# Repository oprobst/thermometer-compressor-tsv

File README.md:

# thermometer-compressor-tsv

Basicly this is a thermometer. It measures up to 3 values within a hirh range of (min. -50 to 350 degrees) using Thermoelement sensors. Additionally a port for DS18B20 is implemented (usually -55 to 125 degrees).
It is equiped with a display and a hard coded alarm limit.

Major requirement is to keep it simple (pure arduino code only) and modular (modules should be easy replaceable).

# Software

I kept the whole logic in this single script to make it easily adjustable for beginners. So there is just one arduino file.

## Arduino libraries in use
* U8g2 (version 2.28.10) Control LCD Display with ST7820 driver.
* OneWire (version 2.3.5) OneWire Bus protocol and driver.
* DallasTemperature (version 3.9.0) Helper library to maintain DS18S20 Temperature sensor.
* Adafruit MAX31855K (version 1.3.0) For reading the MAX 31855K Temperature sensors
* Adafruit BusIO (version 1.7.2) dependency of Adafruit MAX31855 library.

## Functionality

In general, this script consists of 3 major parts:

  1. Get temperature from a bunch of Dallas DS18B20 OneWires sensors. 
     These sensors usually range from -55 ... +85 °C, which is fine for room and outdoor temperature.
  2. Get up to 3 temperatures from K-Typ Thermoelements connected to the µController by a MAX31855 Chip . 
     The design focus on breakout modules easily be added to the ciruit and are replaceable in case of a defect.
     Range depends on type, up to > +1000 °C.
  3. A UI part for a display via the U8g2 lib.

## Components
Goal is to keep the amount of soldered component small and to use standardized plug-in modules. They can be replaced in case of a damage.

### Moduls
* [Arduino Nano (or clone)](https://www.reichelt.de/arduino-nano-v3-atmega-328-mini-usb-arduino-nano-p142943.html?PROVID=2788&gclid=Cj0KCQjw3duCBhCAARIsAJeFyPWbRqnDvxeFE9hGWIxeH9UpAeioCHqXIbZ7PTT7xyMbCtL9xDiokTYaAkQkEALw_wcB)
* [LCD Display 20x4 Character ](https://eckstein-shop.de/Graphic-128x64-LCD-Display-Module-12864-White-on-Blue-5V-Header-Strip?curr=EUR&gclid=Cj0KCQjw3duCBhCAARIsAJeFyPV9fqUd5TVanYePv4DA6xzIegzKWH7t7PSGK8yXDp_RgOqrNXzDfOYaAqsnEALw_wcB)
* 3x [Thermosensor MAX31855 Module](https://www.androegg.de/?product=max31855-k-type-temperatur-sensor-spi-konverter-modul)
* 3x [Rohranlegefühler Typ K (or similar)](https://www.sensorshop24.de/rohranlegefuehler-mit-alu-prisma-mit-nicr-ni-typ-k)
* [12V buzzer](https://www.conrad.de/de/p/tru-components-1567766-piezo-signalgeber-geraeusch-entwicklung-105-db-spannung-12-v-intervallton-1-st-1567766.html)

### On Board
|  ID  | Description |
| --- | -------- |
| R1 | 4,7 kOhm |
| R2 | 150 Ohm  |
| R3 | 10 kOhm  |
| R4 | 10 kOhm Potentiometer (optional) If display circuit has none included |
| U1 | [N-Channel Mosfet](https://www.conrad.de/de/p/infineon-technologies-irlz44npbf-mosfet-1-hexfet-110-w-to-220-162877.html) with 5V Logic-Level Gate |
| IC1 | 7805 Linear Regulator or 5V Output DC/DC Regulator |
| C1 | 330 nF Ceramic Condensator |
| C2 | 100 nF Ceramic Condensator |
| C4 | 220 µF Electrolyte Condensator |
| D1 | 1N4007 Diode |

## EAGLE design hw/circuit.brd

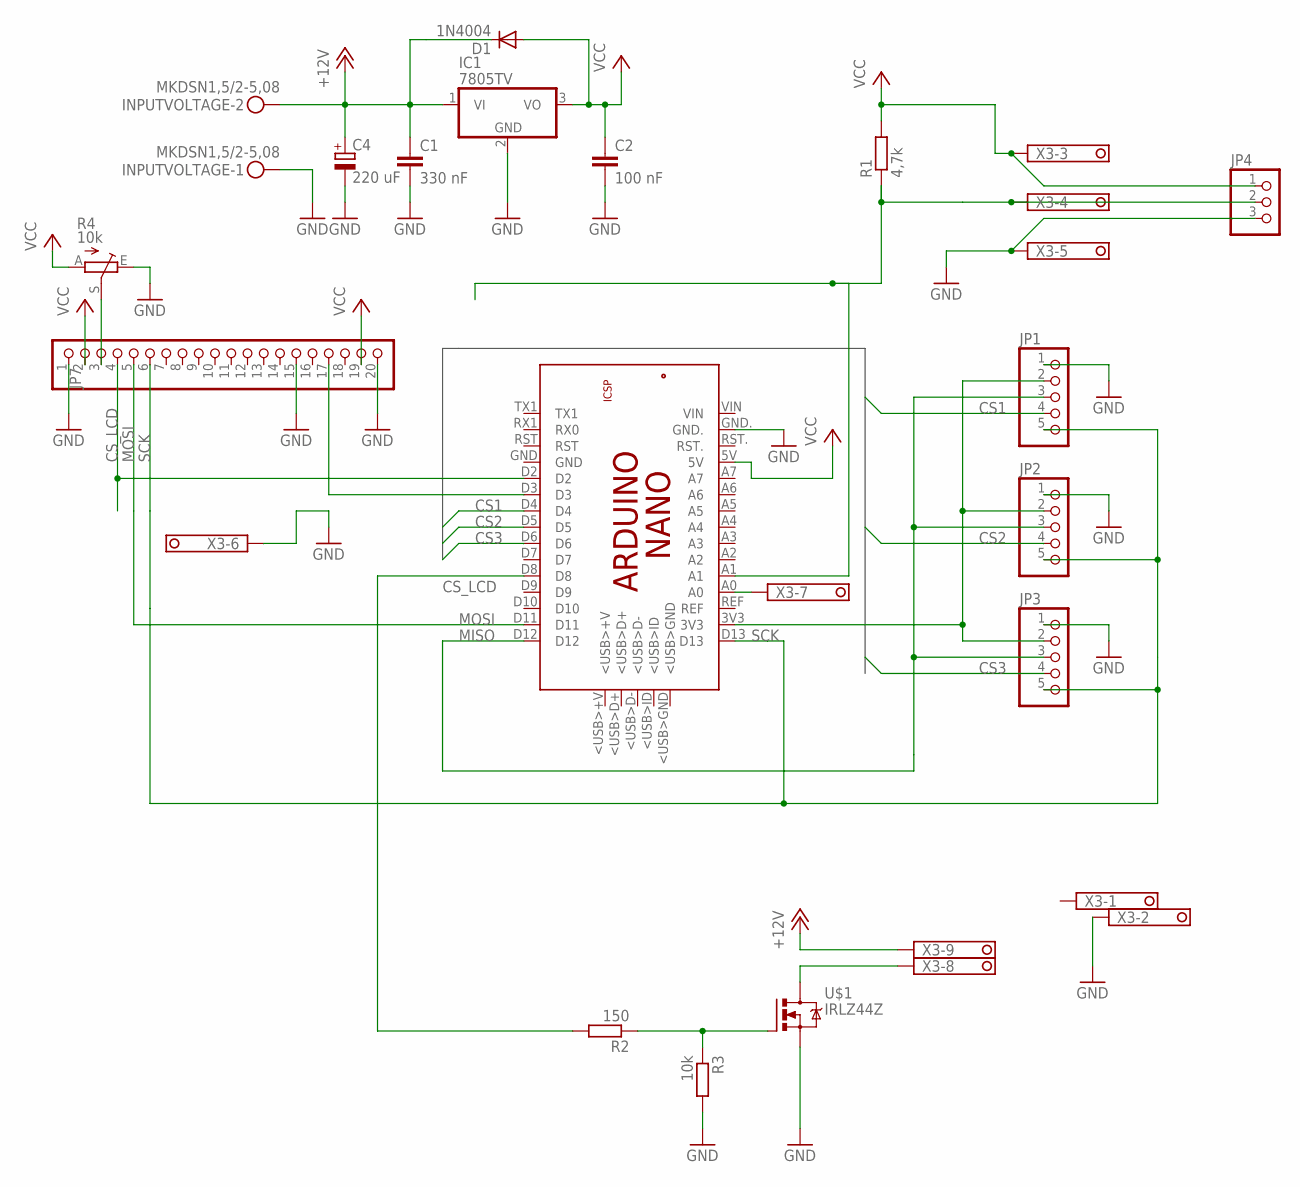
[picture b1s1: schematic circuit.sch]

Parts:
C1: 330 nF; C1206
C2: 100 nF; C0603
C4: 220 uF; E3,5-8
D1: 1N4004; DO41-10
IC1: 7805TV; TO220V
INPUTVOLTAGE: MKDSN1,5/2-5,08
JP1, JP2, JP3: PINHD-1X5; 1X05
JP4: PINHD-1X3; 1X03
JP7: PINHD-1X20; 1X20
PCB1: ARDUINO_NANO
R1: 4,7k; 0309/12
R2: 150; 0309/12
R3: 10k; 0309/12
R4: 10k; B64Y
U$1: IRLZ44Z; TO220BH
X3: 1751316

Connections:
+12V: C1.1, C4.+, D1.C, IC1.1 (VI), INPUTVOLTAGE.2, X3.9
CS1: JP1.4, PCB1.D4
CS2: JP2.4, PCB1.D5
CS3: JP3.4, PCB1.D6
CS_LCD: JP7.4, PCB1.D2
GND: C1.2, C2.2, C4.-, IC1.2 (GND), INPUTVOLTAGE.1, JP1.1, JP2.1, JP3.1, JP4.3, JP7.1, JP7.15, JP7.20, PCB1.GND., R3.2, R4.E, U$1.S, X3.2, X3.5, X3.6
MISO: JP1.3, JP2.3, JP3.3, PCB1.D12
MOSI: JP7.5, PCB1.D11
unnamed: JP7.17, PCB1.D3
unnamed: JP4.2, PCB1.A1, R1.1, X3.4
unnamed: R2.1, R3.1, U$1.G
unnamed: U$1.D, X3.8
unnamed: PCB1.A0, X3.7
unnamed: PCB1.D8, R2.2
unnamed: JP1.2, JP2.2, JP3.2, PCB1.3V3
unnamed: JP7.3, R4.S
SCK: JP1.5, JP2.5, JP3.5, JP7.6, PCB1.D13
VCC: C2.1, D1.A, IC1.3 (VO), JP4.1, JP7.2, JP7.19, PCB1.5V, R1.2, R4.A, X3.3

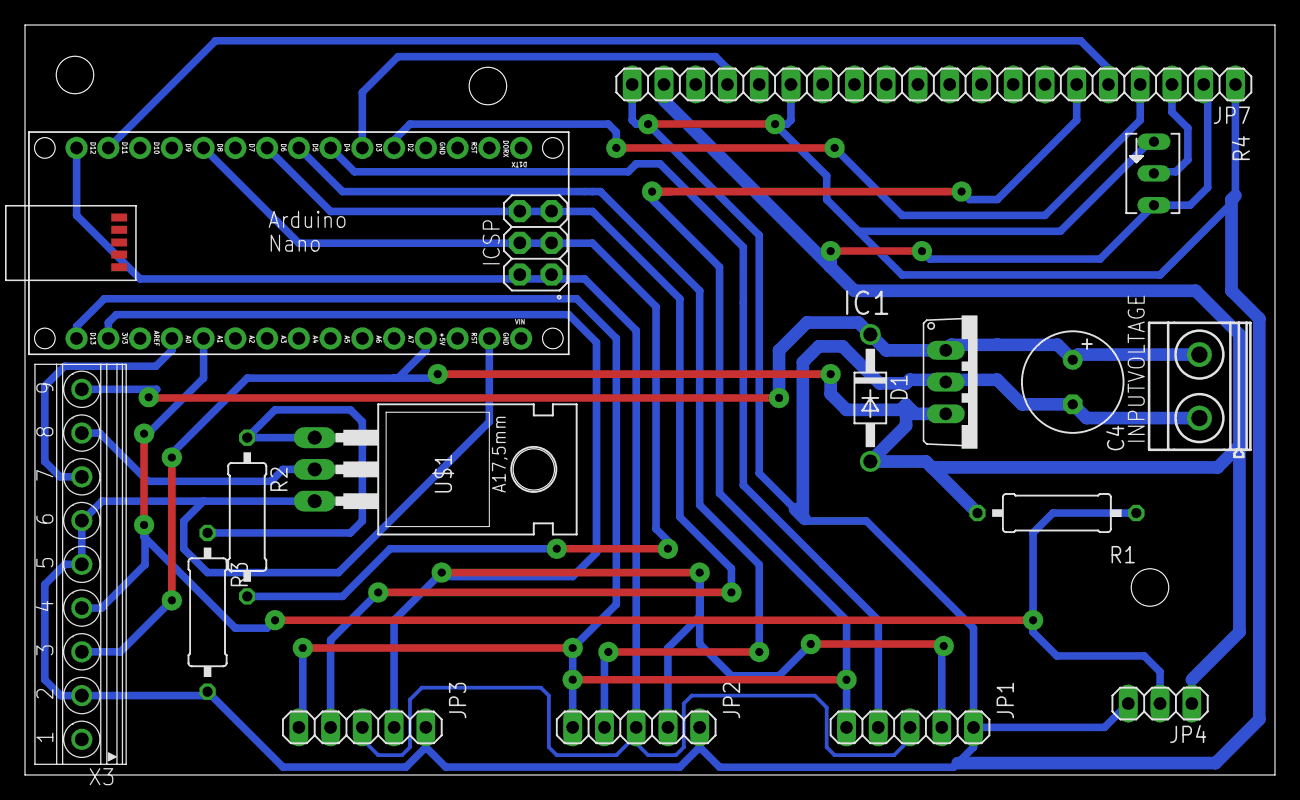
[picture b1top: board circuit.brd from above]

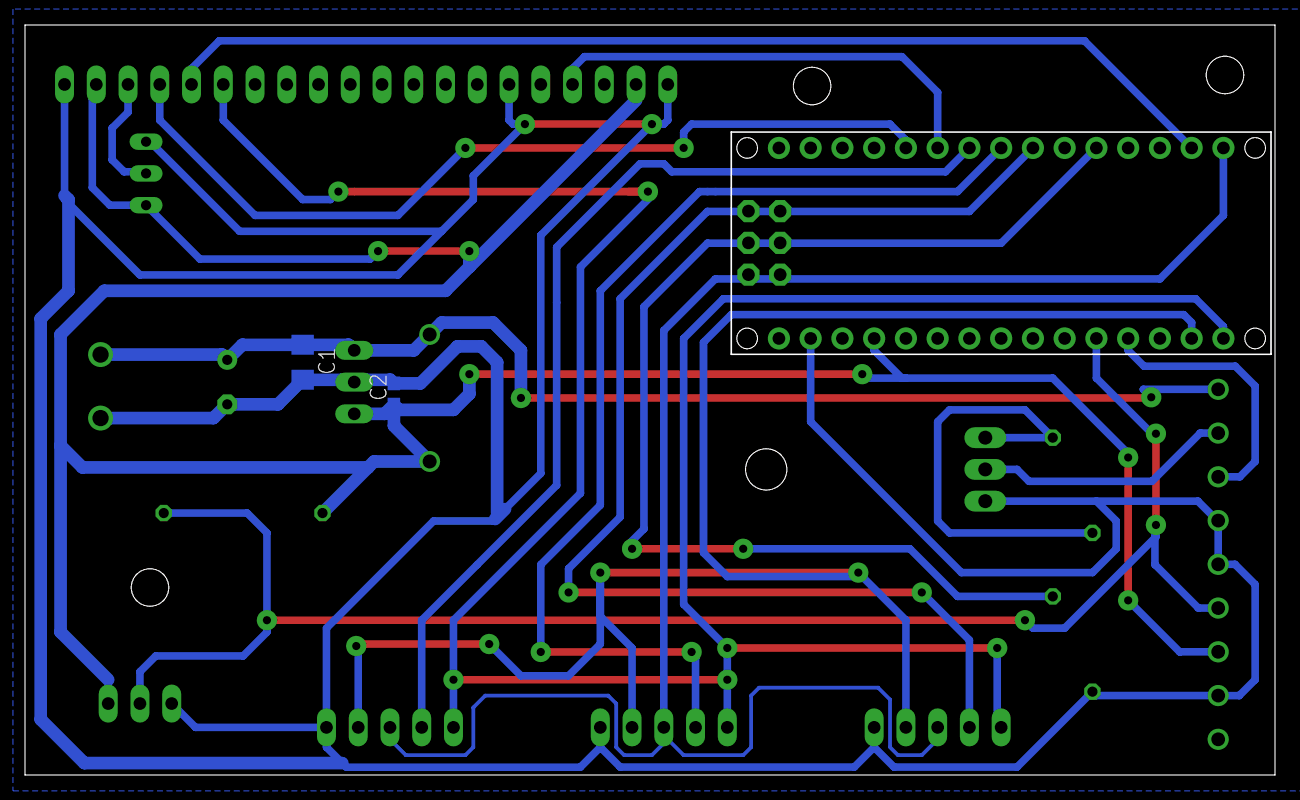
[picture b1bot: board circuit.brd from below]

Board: 2 copper layers, 99.9 x 59.9 mm, 18 parts (2 on the bottom side), 18 nets.

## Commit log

2021-04-04 Initial readme version
2021-04-04 Images board and circuit added
2021-04-04 Prototype version - initial commit
2021-04-04 V2 - Circuit is functional
2021-04-04 Fixed Table
